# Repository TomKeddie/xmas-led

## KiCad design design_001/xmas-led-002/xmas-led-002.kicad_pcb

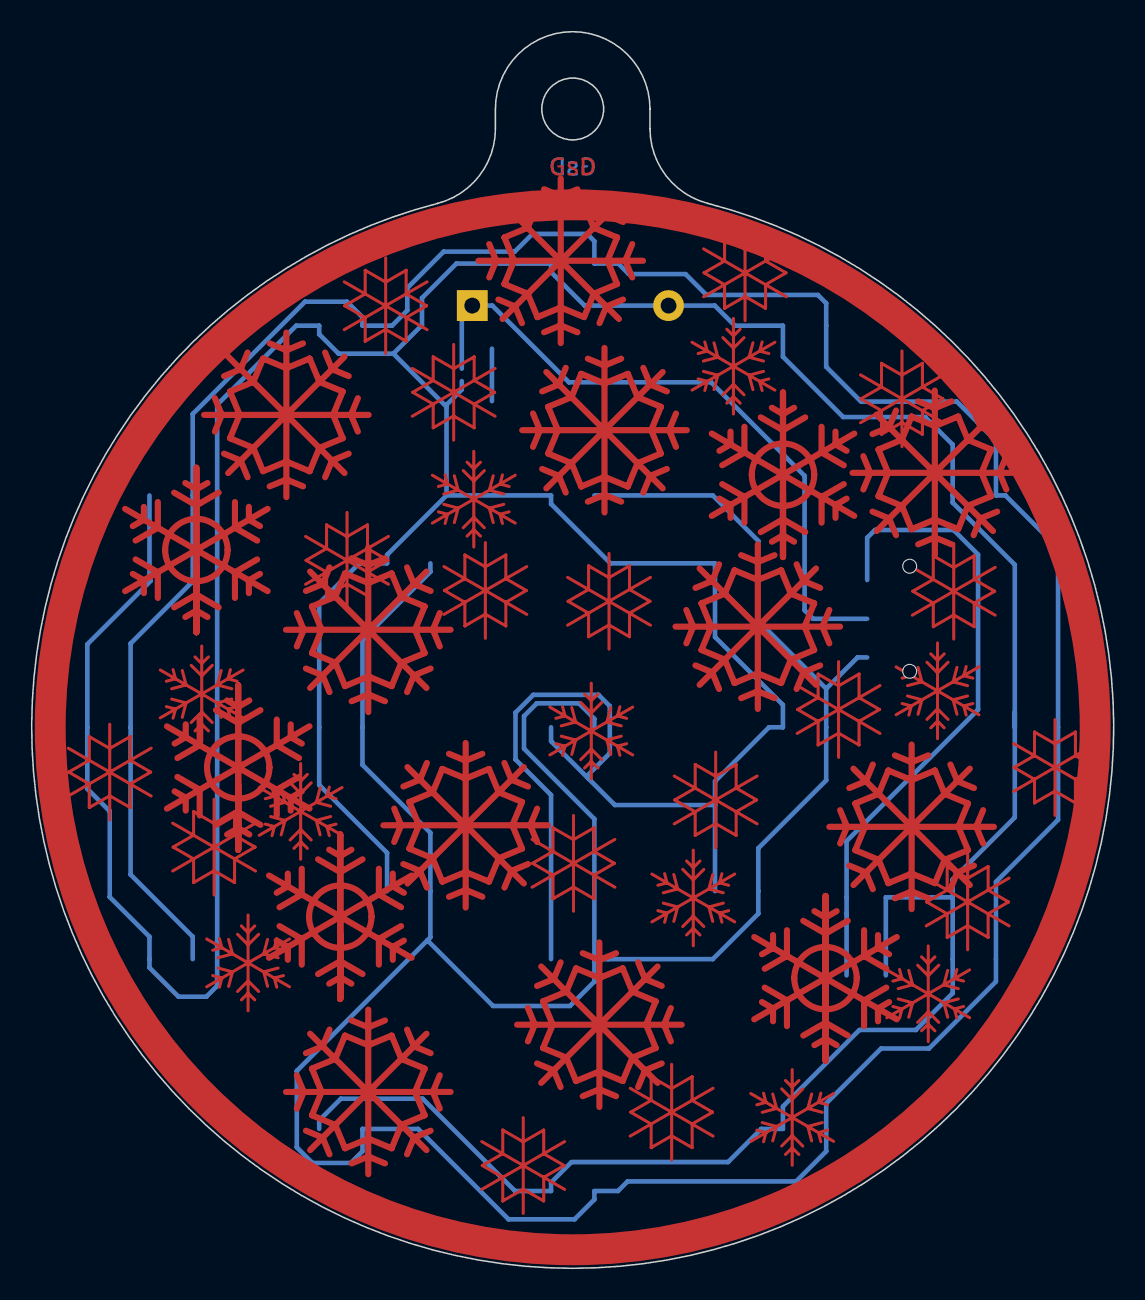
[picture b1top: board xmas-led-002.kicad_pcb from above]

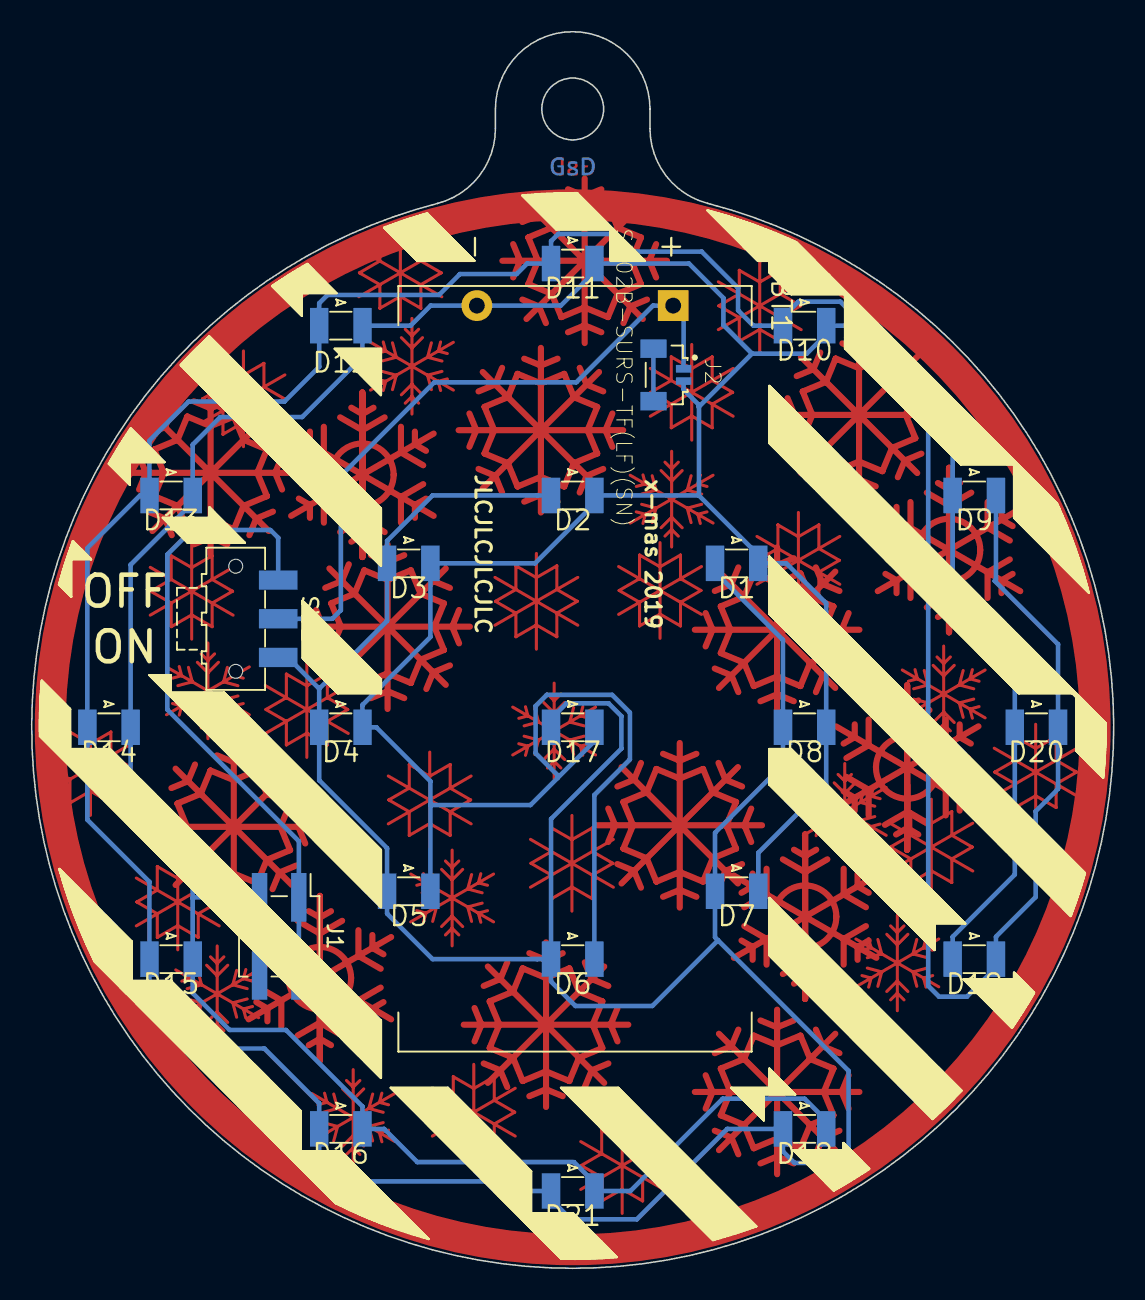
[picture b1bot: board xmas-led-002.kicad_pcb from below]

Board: 2 copper layers, 70.0 x 80.0 mm, 25 parts (25 on the bottom side), 5 nets.

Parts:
BT1: Battery; Keystone_2468_2xAAA
D1, D2, D3, D4, D5, D6, D7, D8, D9, D10, D11, D12, D13, D14, D15, D16, D17, D18, D19, D20, D21: LED_RGB_SLOW; LED_0807
J1: Conn_02x02_Odd_Even; PinHeader_2x02_P2.54mm_Vertical_SMD
J2: SM02B-SURS-TF(LF)(SN); JST_SM02B-SURS-TF(LF)(SN)
SW1: SW_SPDT; SW_SPDT_CK-JS102011SAQN

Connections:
GND: BT1.2, D1.1, D2.1, D3.1, D4.1, D5.1, D6.1, D7.1, D8.1, D9.1, D10.1, D11.1, D12.1, D13.1, D14.1, D15.1, D16.1, D17.1, D18.1, D19.1, D20.1, D21.1, J1.3, J1.4, J2.2
unnamed: BT1.1, J2.1, SW1.2
unnamed: D1.2, D2.2, D3.2, D4.2, D5.2, D6.2, D7.2, D8.2, D9.2, D10.2, D11.2, D12.2, D13.2, D14.2, D15.2, D16.2, D17.2, D18.2, D19.2, D20.2, D21.2, SW1.3
unnamed: J1.1, J1.2, SW1.1
unnamed: J2.S1, J2.S2

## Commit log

2019-11-28 xmas-led-002: add 2 layer design, fixed schematic & pcb
2019-11-28 Added Keystone_2468_2xAAA footprint
